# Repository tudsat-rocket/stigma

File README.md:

# Stigma

the core- and mission board for our new flight computer

## Core Board
The core board will be placed on the mission board and will contain all basic and always-needed stuff. Powered by an STM32H7

## Mission Board
The mission board will contain all the other components but may change for future use cases of the core board.

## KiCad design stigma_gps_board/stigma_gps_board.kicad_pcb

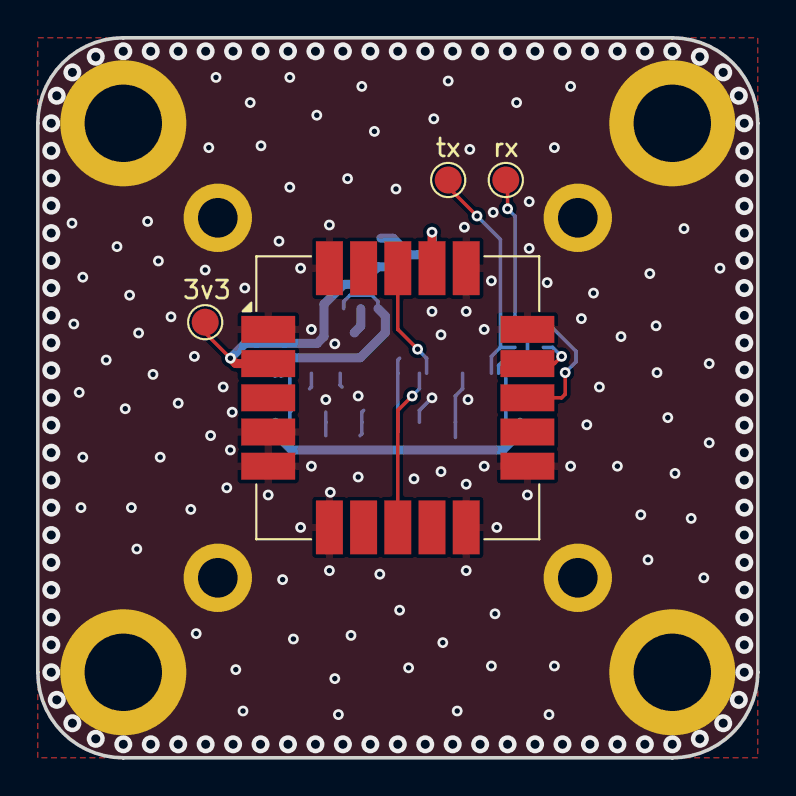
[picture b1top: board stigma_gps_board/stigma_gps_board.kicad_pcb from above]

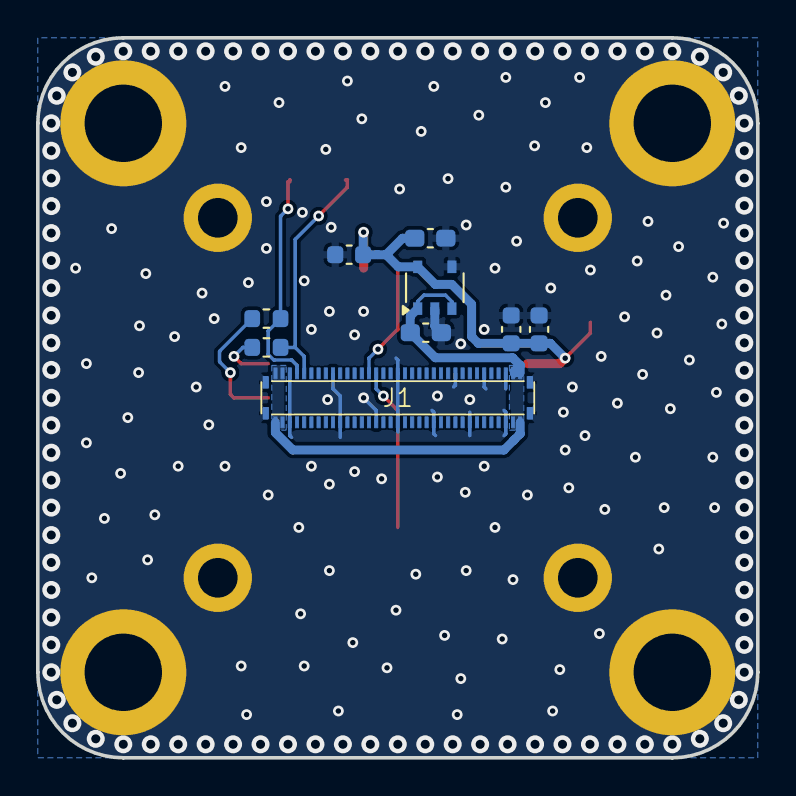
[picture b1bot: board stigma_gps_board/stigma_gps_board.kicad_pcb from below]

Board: 2 copper layers, 40.0 x 40.0 mm, 21 parts (9 on the bottom side), 9 nets.

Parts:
C1, C2: 1uF; C_0603_1608Metric_Pad1.08x0.95mm_HandSolder
C3, C4, C5: 100n; C_0603_1608Metric
H1, H2, H3, H4: MountingHole_Pad; MountingHole_2.2mm_M2_ISO14580_Pad
H5, H6, H7, H8: MountingHole_Pad; MountingHole_4.3mm_M4_ISO14580_Pad
J1: DF40GB-70DP-0.4V; DF40GB-70DP-0.4V-plug
L1, L2: BEAD; L_0603_1608Metric
TP1: tx; TestPoint_Pad_D1.5mm
TP2: rx; TestPoint_Pad_D1.5mm
TP3: 3v3; TestPoint_Pad_D1.5mm
U1: NCP115AMX120TCG; TSOP-5_1.65x3.05mm_P0.95mm
U2: SAM-M10Q; ublox_SAM-M8Q_HandSolder

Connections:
+3.3V: C2.2, C3.2, C4.2, C5.2, TP3.1, U1.5 (OUT), U2.2 (VCC_IO), U2.17 (VCC)
+5V: C1.2, J1.1, J1.2, J1.34, J1.35, J1.36, J1.37, J1.69, J1.70, U1.1 (IN), U1.3 (EN)
GND: C1.1, C2.1, C3.1, C4.1, C5.1, H1.1, H2.1, H3.1, H4.1, H5.1, H6.1, H7.1, H8.1, J1.3, J1.9, J1.18, J1.26, J1.30, J1.33, J1.38, J1.45, J1.50, J1.53, J1.58, J1.63, J1.68, J1.SH (Shield), U1.2 (GND), U1.4 (NC), U2.1 (GND), U2.4 (GND), U2.5 (GND), U2.6 (GND), U2.10 (GND), U2.11 (GND), U2.15 (GND), U2.16 (GND), U2.20 (GND)
GPS_RESET: J1.14, U2.18 (~RESET)
GPS_SAFEBOOT: J1.15, U2.8 (~SAFEBOOT)
unnamed: L1.1, U2.14 (RXD)
unnamed: L2.1, U2.13 (TXD)
UART8_RX_GPS: J1.4, L2.2, TP2.1
UART8_TX_GPS: J1.5, L1.2, TP1.1

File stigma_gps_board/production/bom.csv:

Designator,Footprint,Quantity,Value,LCSC Part #
"C1, C2",0603,2,1uF,C15849
"C3, C4, C5",0603,3,100n,C14663
J1,DF40GB-70DP-0.4V-plug,1,DF40GB-70DP-0.4V,C2692097
L1,0603,1,BEAD,C19330
L2,0603,1,BEAD,
TP1,TestPoint_Pad_D1.5mm,1,tx,
TP2,TestPoint_Pad_D1.5mm,1,rx,
TP3,TestPoint_Pad_D1.5mm,1,3v3,
U1,TSOP-5_1.65x3.05mm_P0.95mm,1,NCP115AMX120TCG,C603505

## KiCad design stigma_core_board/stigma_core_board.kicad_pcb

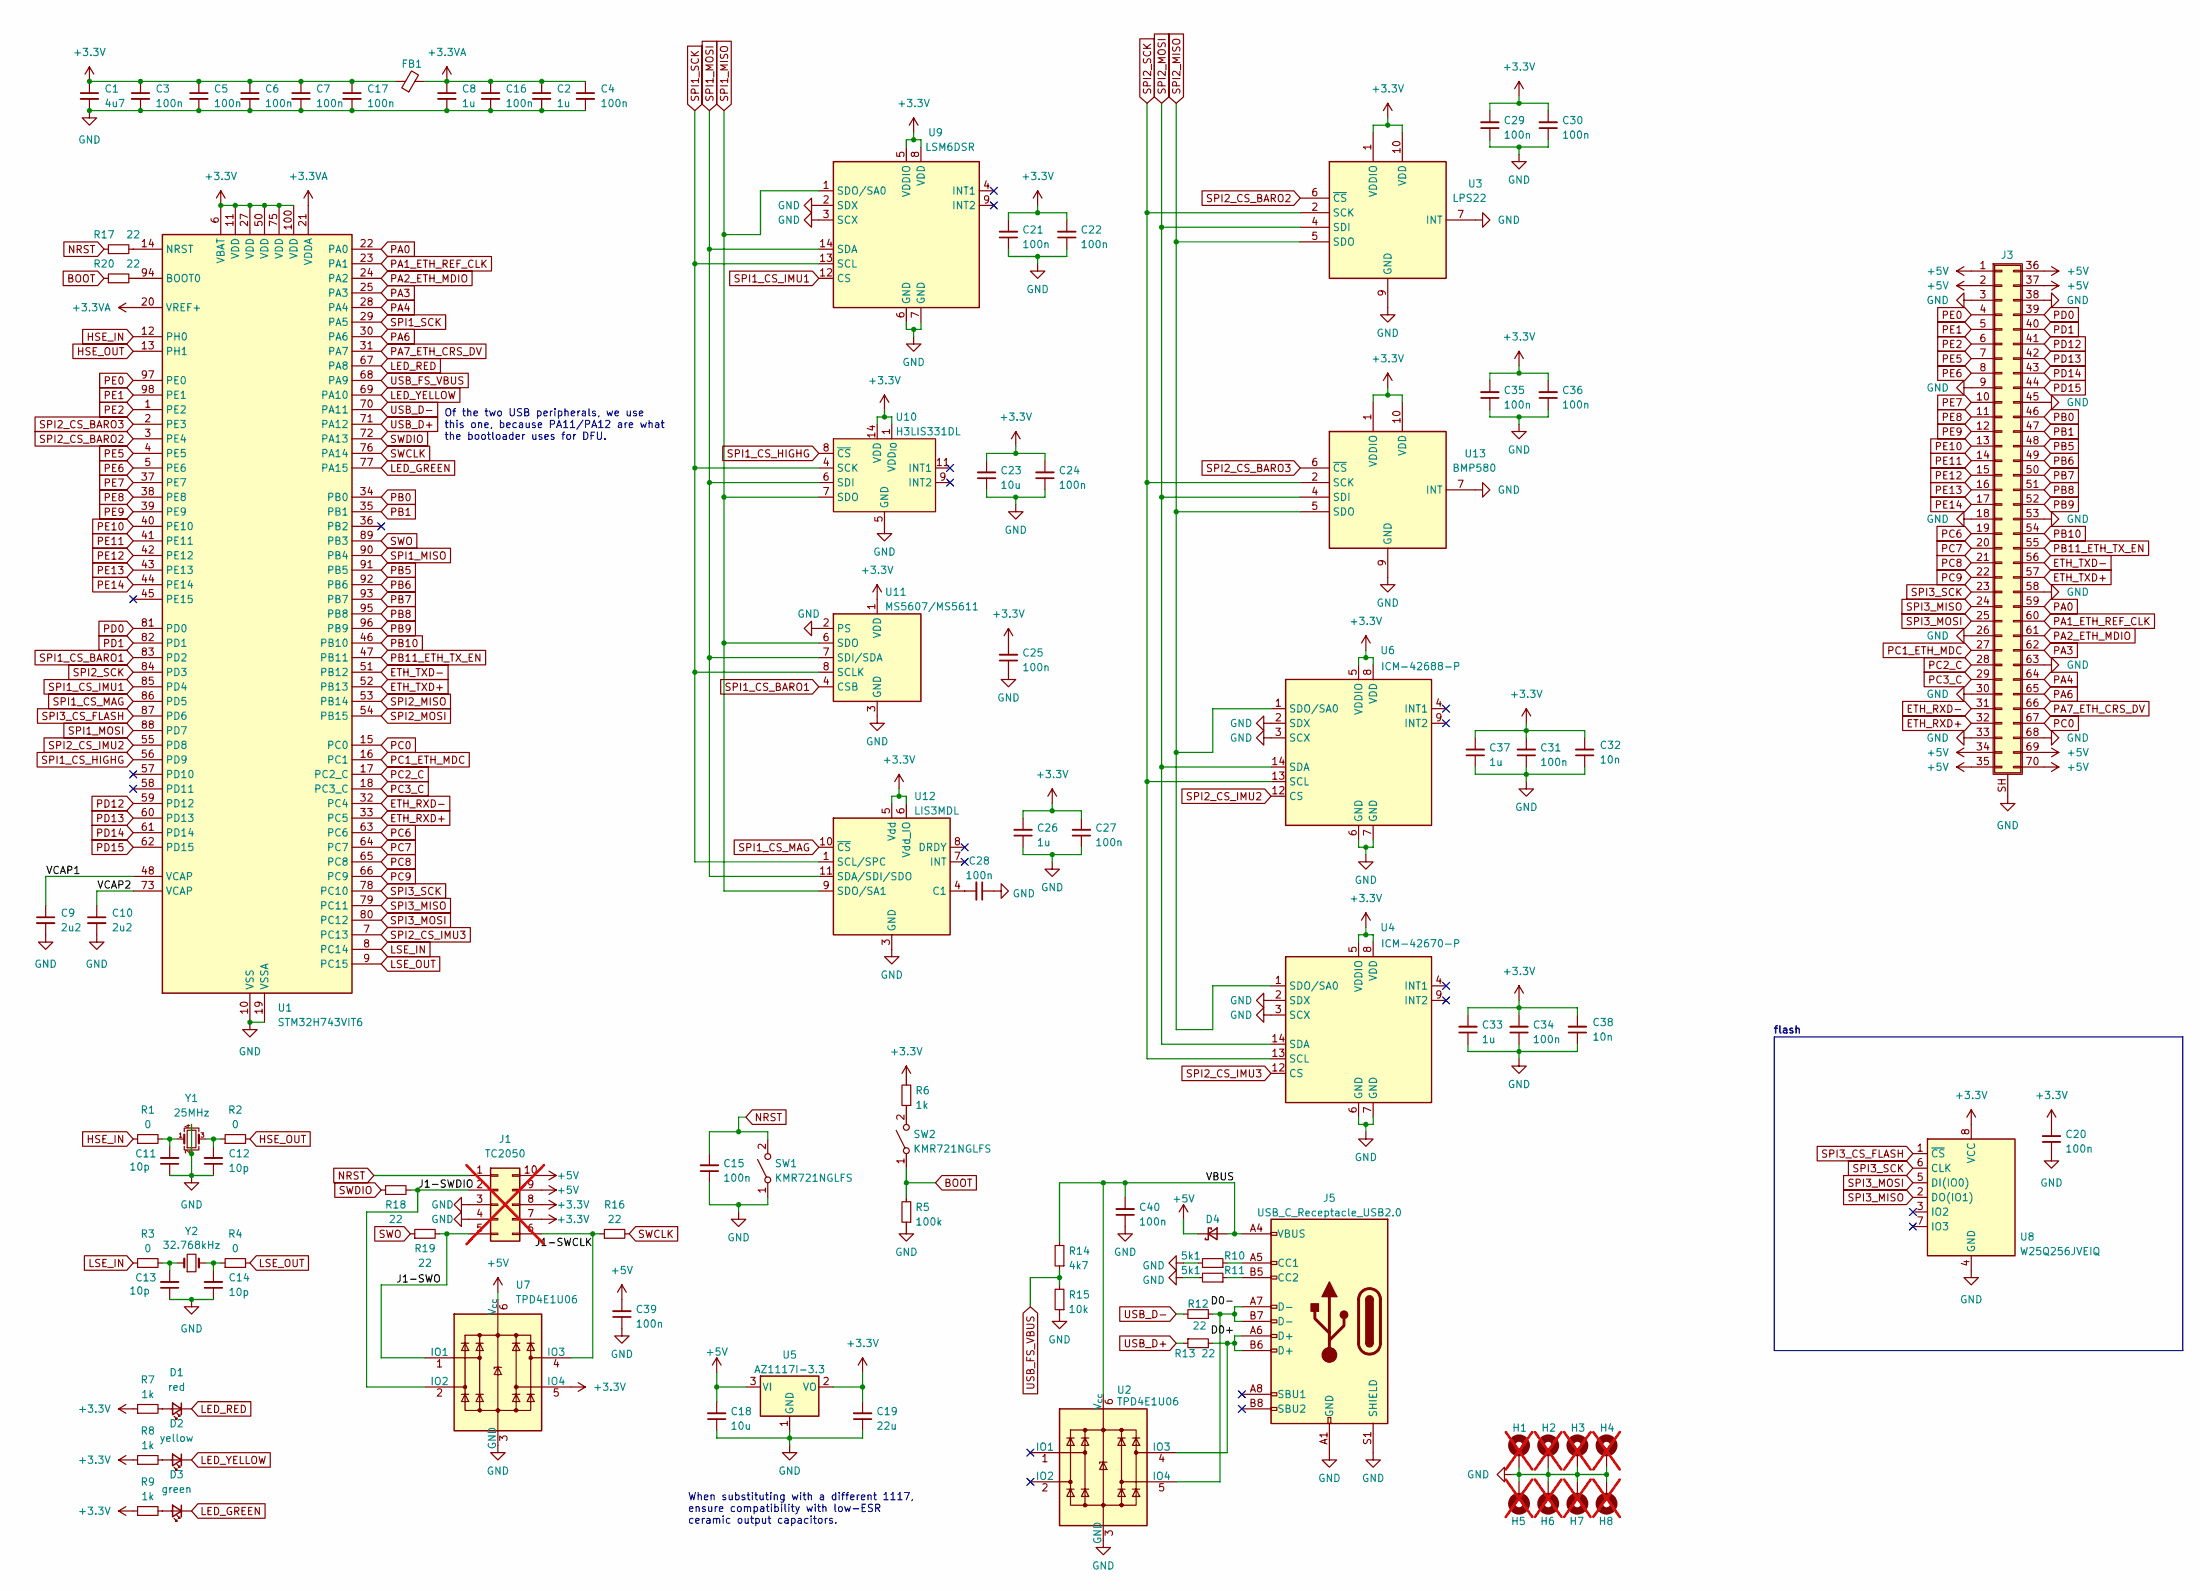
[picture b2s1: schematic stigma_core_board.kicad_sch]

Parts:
C1: 4u7; C_0603_1608Metric; LCSC C19666
C2, C8: 1u; C_0402_1005Metric; LCSC C52923
C3, C4, C5, C6, C7, C16, C17: 100n; C_0402_1005Metric; LCSC C1525
C9, C10: 2u2; C_0402_1005Metric; LCSC C12530
C11, C12, C13, C14: 10p; C_0402_1005Metric; LCSC C32949
C15, C20, C21, C22, C24, C25, C27, C28, C29, C30, C31, C34, C35, C36, C39, C40: 100n; C_0402_1005Metric; Part# CL10B104KB8NNNC; LCSC C1525
C18, C23: 10u; C_0603_1608Metric; Part# CL31B106KAHNNNE; LCSC C19702
C19: 22u; C_0603_1608Metric; Part# CL31A226KAHNNNE; LCSC C86295
C26, C33, C37: 1u; C_0402_1005Metric; Part# CL21A105KBCLNNC; LCSC C52923
C32, C38: 10n; C_0402_1005Metric; Part# CL10B104KB8NNNC; LCSC C15195
D1: red; LED_0603_1608Metric; LCSC C2286
D2: yellow; LED_0603_1608Metric; LCSC C72038
D3: green; LED_0603_1608Metric; LCSC C965804
D4: D_SOD-123; Part# PMEG3020EH,115; LCSC C8598
FB1: FerriteBead_Small; R_0603_1608Metric; LCSC C1002
H1, H2, H3, H4: MountingHole_Pad; MountingHole_4.3mm_M4_ISO14580_Pad; not fitted
H5, H6, H7, H8: MountingHole_Pad; MountingHole_2.2mm_M2_ISO14580_Pad; not fitted
J1: TC2050; Tag-Connect_TC2050-IDC-FP_2x05_P1.27mm_Vertical; not fitted
J3: CONN PLUG 70POS SMD GOLD; DF40GB-70DP-0.4V-plug; LCSC# C2692097
J5: USB_C_Receptacle_USB2.0; USB_C_Receptacle_Palconn_UTC16-G; Part# KH-TYPE-C-16P; LCSC C709357
R1, R2, R3, R4: 0; R_0402_1005Metric; LCSC C17168
R5: 100k; R_0402_1005Metric; Part# RC0603FR-0710KL; LCSC C25741
R6: 1k; R_0402_1005Metric; Part# RC0603FR-0710KL; LCSC C11702
R7, R8, R9: 1k; R_0402_1005Metric; LCSC C11702
R10, R11: 5k1; R_0402_1005Metric; Part# RC0603FR-075K1L; LCSC C25905
R12, R13: 22; R_0402_1005Metric; Part# RC0603FR-0722RL; LCSC C25092
R14: 4k7; R_0402_1005Metric; Part# RC0603FR-0710KL; LCSC C25900
R15: 10k; R_0402_1005Metric; Part# RC0603FR-0710KL; LCSC C25744
R16, R17, R18, R19, R20: 22; R_0402_1005Metric; Part# RC0603FR-0710KL; LCSC C25092
SW1, SW2: KMR721NGLFS; SW_Push_1P1T_NO_CK_KMR2; Part# KMR721NGLFS; LCSC C2911418
U1: STM32H743VIT6; LQFP-100_14x14mm_P0.5mm; LCSC C114409
U2, U7: TPD4E1U06; SOT-563; LCSC C527516
U3: LPS22; ST_HLGA-10_2x2mm_P0.5mm_LayoutBorder3x2y; LCSC C2827824
U4: ICM-42670-P; LGA-14_3x2.5mm_P0.5mm_LayoutBorder3x4y; LCSC C3288646
U5: AZ1117I-3.3; SOT-223-3_TabPin2; Part# AZ1117CH-3.3TRG1; LCSC C92102
U6: ICM-42688-P; LGA-14_3x2.5mm_P0.5mm_LayoutBorder3x4y; Part# LSM6DSRTR; LCSC C1850418
U8: W25Q256JVEIQ; WSON-8-1EP_8x6mm_P1.27mm_EP3.4x4.3mm; LCSC C97522
U9: LSM6DSR; LGA-14_3x2.5mm_P0.5mm_LayoutBorder3x4y; Part# LSM6DSRTR; LCSC C784817
U10: H3LIS331DL; LGA-16_3x3mm_P0.5mm_LayoutBorder3x5y; Part# H3LIS331DLTR; DigiKey# 497-13903-1-ND
U11: MS5607/MS5611; LGA-8_3x5mm_P1.25mm; Part# MS561101BA03-50; DigiKey# 223-1622-1-ND
U12: LIS3MDL; LGA-12_2x2mm_P0.5mm; Part# LIS3MDLTR; DigiKey# 497-13892-1-ND
U13: BMP580; ST_HLGA-10_2x2mm_P0.5mm_LayoutBorder3x2y; LCSC C22391138
Y1: 25MHz; Crystal_SMD_3225-4Pin_3.2x2.5mm; LCSC C9006
Y2: 32.768kHz; Crystal_SMD_3215-2Pin_3.2x1.5mm; LCSC C70509

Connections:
+3.3V: C1.1, C3.1, C5.1, C6.1, C7.1, C17.1, C19.2, C20.2, C21.2, C22.2, C23.2, C24.2, C25.2, C26.2, C27.2, C29.2, C30.2, C31.2, C32.2, C33.2, C34.2, C35.2, C36.2, C37.2, C38.2, FB1.1, J1.7, J1.8, R6.2, R7.1, R8.1, R9.1, U1.6 (VBAT), U1.11 (VDD), U1.27 (VDD), U1.50 (VDD), U1.75 (VDD), U1.100 (VDD), U3.1 (VDDIO), U3.10 (VDD), U4.5 (VDDIO), U4.8 (VDD), U5.2 (VO), U6.5 (VDDIO), U6.8 (VDD), U7.5 (IO4), U8.8 (VCC), U9.5 (VDDIO), U9.8 (VDD), U10.1 (VDD_{IO}), U10.14 (VDD), U10.15 (reserved), U11.1 (VDD), U12.5 (Vdd), U12.6 (Vdd_IO), U13.1 (VDDIO), U13.10 (VDD)
+3.3VA: C2.1, C4.1, C8.1, C16.1, FB1.2, U1.20 (VREF+), U1.21 (VDDA)
+5V: C18.2, C39.2, D4.1 (K), J1.9, J1.10, J3.1, J3.2, J3.34, J3.35, J3.36, J3.37, J3.69, J3.70, U5.3 (VI), U7.6 (V_{cc})
/D0+: J5.A6 (D+), J5.B6 (D+), R13.2, U2.4 (IO3)
/D0-: J5.A7 (D-), J5.B7 (D-), R12.1, U2.5 (IO4)
/J1-SWDIO: J1.2, R18.2, U7.2 (IO2)
/J1-SWO: J1.5, R19.2, U7.1 (IO1)
/VBUS: C40.2, D4.2 (A), J5.A4 (VBUS), J5.A9 (VBUS), J5.B4 (VBUS), J5.B9 (VBUS), R14.2, U2.6 (V_{cc})
/VCAP1: C9.1, U1.48 (VCAP)
/VCAP2: C10.1, U1.73 (VCAP)
BOOT: R5.2, R20.1, SW2.1 (A)
ETH_RXD+: J3.32, U1.33 (PC5)
ETH_RXD-: J3.31, U1.32 (PC4)
ETH_TXD+: J3.57, U1.52 (PB13)
ETH_TXD-: J3.56, U1.51 (PB12)
GND: C1.2, C2.2, C3.2, C4.2, C5.2, C6.2, C7.2, C8.2, C9.2, C10.2, C11.1, C12.1, C13.1, C14.1, C15.1, C16.2, C17.2, C18.1, C19.1, C20.1, C21.1, C22.1, C23.1, C24.1, C25.1, C26.1, C27.1, C28.1, C29.1, C30.1, C31.1, C32.1, C33.1, C34.1, C35.1, C36.1, C37.1, C38.1, C39.1, C40.1, H1.1, H2.1, H3.1, H4.1, H5.1, H6.1, H7.1, H8.1, J1.3, J1.4, J3.3, J3.9, J3.18, J3.26, J3.30, J3.33, J3.38, J3.45, J3.53, J3.58, J3.63, J3.68, J3.SH (Shield), J5.A1 (GND), J5.A12 (GND), J5.B1 (GND), J5.B12 (GND), J5.S1 (SHIELD), R5.1, R10.2, R11.2, R15.1, SW1.1 (A), U1.10 (VSS), U1.19 (VSSA), U1.26 (VSS), U1.49 (VSS), U1.74 (VSS), U1.99 (VSS), U2.3 (GND), U3.3 (GND), U3.7 (INT), U3.8 (GND), U3.9 (GND), U4.2 (SDX), U4.3 (SCX), U4.6 (GND), U4.7 (GND), U5.1 (GND), U6.2 (SDX), U6.3 (SCX), U6.6 (GND), U6.7 (GND), U7.3 (GND), U8.4 (GND), U9.2 (SDX), U9.3 (SCX), U9.6 (GND), U9.7 (GND), U10.5 (GND), U10.10 (reserved), U10.12 (GND), U10.13 (GND), U10.16 (GND), U11.2 (PS), U11.3 (GND), U12.2 (GND), U12.3 (GND), U12.12 (GND), U13.3 (GND), U13.7 (INT), U13.8 (GND), U13.9 (GND), Y1.2, Y1.4
HSE_IN: R1.1, U1.12 (PH0)
HSE_OUT: R2.2, U1.13 (PH1)
LED_GREEN: D3.1 (K), U1.77 (PA15)
LED_RED: D1.1 (K), U1.67 (PA8)
LED_YELLOW: D2.1 (K), U1.69 (PA10)
LSE_IN: R3.1, U1.8 (PC14)
LSE_OUT: R4.2, U1.9 (PC15)
NRST: C15.2, J1.1, R17.1, SW1.2 (B)
unnamed: C11.2, R1.2, Y1.1
unnamed: C12.2, R2.1, Y1.3
unnamed: C13.2, R3.2, Y2.1
unnamed: C14.2, R4.1, Y2.2
unnamed: D1.2 (A), R7.2
unnamed: D2.2 (A), R8.2
unnamed: D3.2 (A), R9.2
unnamed: J1.6, R16.1, U7.4 (IO3)
unnamed: J5.A5 (CC1), R10.1
unnamed: J5.B5 (CC2), R11.1
unnamed: R6.1, SW2.2 (B)
unnamed: R20.2, U1.94 (BOOT0)
unnamed: R17.2, U1.14 (NRST)
unnamed: C28.2, U12.4 (C1)
PA0: J3.59, U1.22 (PA0)
PA1_ETH_REF_CLK: J3.60, U1.23 (PA1)
PA2_ETH_MDIO: J3.61, U1.24 (PA2)
PA3: J3.62, U1.25 (PA3)
PA4: J3.64, U1.28 (PA4)
PA6: J3.65, U1.30 (PA6)
PA7_ETH_CRS_DV: J3.66, U1.31 (PA7)
PB0: J3.46, U1.34 (PB0)
PB1: J3.47, U1.35 (PB1)
PB5: J3.48, U1.91 (PB5)
PB6: J3.49, U1.92 (PB6)
PB7: J3.50, U1.93 (PB7)
PB8: J3.51, U1.95 (PB8)
PB9: J3.52, U1.96 (PB9)
PB10: J3.54, U1.46 (PB10)
PB11_ETH_TX_EN: J3.55, U1.47 (PB11)
PC0: J3.67, U1.15 (PC0)
PC1_ETH_MDC: J3.27, U1.16 (PC1)
PC2_C: J3.28, U1.17 (PC2_C)
PC3_C: J3.29, U1.18 (PC3_C)
PC6: J3.19, U1.63 (PC6)
PC7: J3.20, U1.64 (PC7)
PC8: J3.21, U1.65 (PC8)
PC9: J3.22, U1.66 (PC9)
PD0: J3.39, U1.81 (PD0)
PD1: J3.40, U1.82 (PD1)
PD12: J3.41, U1.59 (PD12)
PD13: J3.42, U1.60 (PD13)
PD14: J3.43, U1.61 (PD14)
PD15: J3.44, U1.62 (PD15)
PE0: J3.4, U1.97 (PE0)
PE1: J3.5, U1.98 (PE1)
PE2: J3.6, U1.1 (PE2)
PE5: J3.7, U1.4 (PE5)
PE6: J3.8, U1.5 (PE6)
PE7: J3.10, U1.37 (PE7)
PE8: J3.11, U1.38 (PE8)
PE9: J3.12, U1.39 (PE9)
PE10: J3.13, U1.40 (PE10)
PE11: J3.14, U1.41 (PE11)
PE12: J3.15, U1.42 (PE12)
PE13: J3.16, U1.43 (PE13)
PE14: J3.17, U1.44 (PE14)
SPI1_CS_BARO1: U1.83 (PD2), U11.4 (CSB), U11.5 (CSB)
SPI1_CS_HIGHG: U1.56 (PD9), U10.8 (~CS)
SPI1_CS_IMU1: U1.85 (PD4), U9.12 (CS)
SPI1_CS_MAG: U1.86 (PD5), U12.10 (~CS)
SPI1_MISO: U1.90 (PB4), U9.1 (SDO/SA0), U10.7 (SDO), U11.6 (SDO), U12.9 (SDO/SA1)
SPI1_MOSI: U1.88 (PD7), U9.14 (SDA), U10.6 (SDI), U11.7 (SDI/SDA), U12.11 (SDA/SDI/SDO)
SPI1_SCK: U1.29 (PA5), U9.13 (SCL), U10.4 (SCK), U11.8 (SCLK), U12.1 (SCL/SPC)
SPI2_CS_BARO2: U1.3 (PE4), U3.6 (~CS)
SPI2_CS_BARO3: U1.2 (PE3), U13.6 (~CS)
SPI2_CS_IMU2: U1.55 (PD8), U6.12 (CS)
SPI2_CS_IMU3: U1.7 (PC13), U4.12 (CS)
SPI2_MISO: U1.53 (PB14), U3.5 (SDO), U4.1 (SDO/SA0), U6.1 (SDO/SA0), U13.5 (SDO)
SPI2_MOSI: U1.54 (PB15), U3.4 (SDI), U4.14 (SDA), U6.14 (SDA), U13.4 (SDI)
SPI2_SCK: U1.84 (PD3), U3.2 (SCK), U4.13 (SCL), U6.13 (SCL), U13.2 (SCK)
SPI3_CS_FLASH: U1.87 (PD6), U8.1 (~CS)
SPI3_MISO: J3.24, U1.79 (PC11), U8.2 (DO(IO1))
SPI3_MOSI: J3.25, U1.80 (PC12), U8.5 (DI(IO0))
SPI3_SCK: J3.23, U1.78 (PC10), U8.6 (CLK)
SWCLK: R16.2, U1.76 (PA14)
SWDIO: R18.1, U1.72 (PA13)
SWO: R19.1, U1.89 (PB3)
USB_D+: R13.1, U1.71 (PA12)
USB_D-: R12.2, U1.70 (PA11)
USB_FS_VBUS: R14.1, R15.2, U1.68 (PA9)

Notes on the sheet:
Of the two USB peripherals, we use this one, because PA11/PA12 are what the bootloader uses for DFU.
flash
When substituting with a different 1117, ensure compatibility with low-ESR ceramic output capacitors.

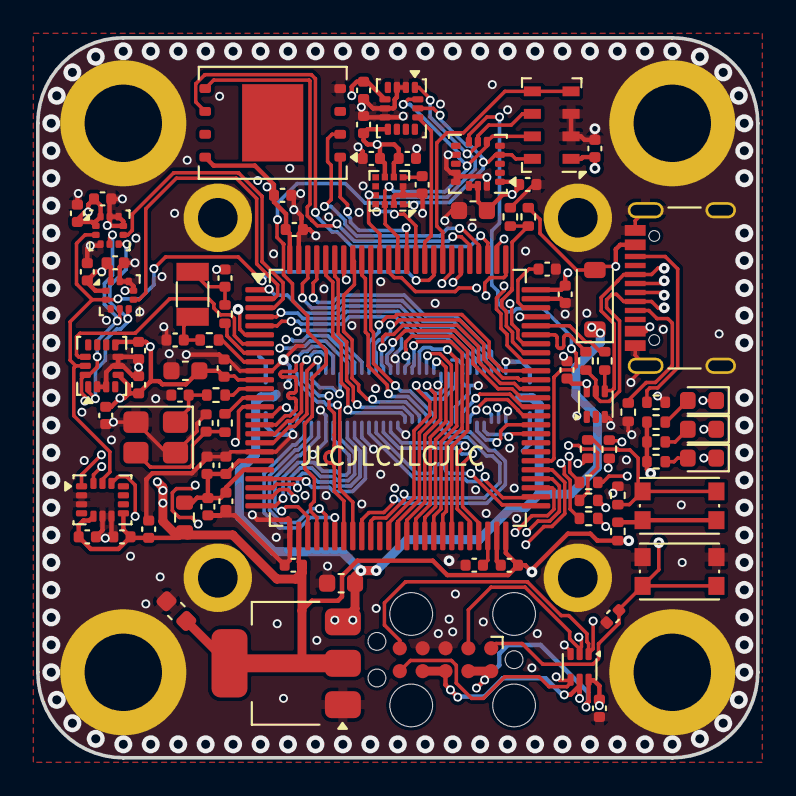
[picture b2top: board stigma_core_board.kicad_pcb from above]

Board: 4 copper layers, 40.0 x 40.0 mm, 93 parts (1 on the bottom side), 105 nets.

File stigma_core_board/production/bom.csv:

Designator,Footprint,Quantity,Value,LCSC Part #
C1,0603,1,4u7,C19666
"C10, C9",0402,2,2u2,C12530
"C11, C12, C13, C14",0402,4,10p,C32949
"C15, C16, C17, C20, C21, C22, C24, C25, C27, C28, C29, C3, C30, C31, C34, C35, C36, C39, C4, C40, C5, C6, C7",0402,23,100n,C1525
"C18, C23",0603,2,10u,C19702
C19,0603,1,22u,C86295
"C2, C26, C33, C37, C8",0402,5,1u,C52923
"C32, C38",0402,2,10n,C15195
D1,0603,1,red,C2286
D2,0603,1,yellow,C72038
D3,0603,1,green,C965804
D4,D_SOD-123,1,~,C8598
FB1,0603,1,FerriteBead_Small,C1002
J1,Tag-Connect_TC2050-IDC-FP_2x05_P1.27mm_Vertical,1,TC2050,
J3,DF40GB-70DP-0.4V-plug,1,CONN PLUG 70POS SMD GOLD,
J5,USB_C_Receptacle_Palconn_UTC16-G,1,USB_C_Receptacle_USB2.0,C709357
"R1, R2, R3, R4",0402,4,0,C17168
"R10, R11",0402,2,5k1,C25905
"R12, R13, R16, R17, R18, R19, R20",0402,7,22,C25092
R14,0402,1,4k7,C25900
R15,0402,1,10k,C25744
R5,0402,1,100k,C25741
"R6, R7, R8, R9",0402,4,1k,C11702
"SW1, SW2",SW_Push_1P1T_NO_CK_KMR2,2,KMR721NGLFS,C2911418
U1,LQFP-100_14x14mm_P0.5mm,1,STM32H743VIT6,C114409
U10,LGA-16_3x3mm_P0.5mm_LayoutBorder3x5y,1,H3LIS331DL,C2655074
U11,LGA-8_3x5mm_P1.25mm,1,MS5607/MS5611,C97627
U12,LGA-12_2x2mm_P0.5mm,1,LIS3MDL,C478483
U13,ST_HLGA-10_2x2mm_P0.5mm_LayoutBorder3x2y,1,BMP580,C22391138
"U2, U7",SOT-563,2,TPD4E1U06,C527516
U3,ST_HLGA-10_2x2mm_P0.5mm_LayoutBorder3x2y,1,LPS22,C2827824
U4,LGA-14_3x2.5mm_P0.5mm_LayoutBorder3x4y,1,ICM-42670-P,C3288646
U5,SOT-223-3_TabPin2,1,AZ1117I-3.3,C92102
U6,LGA-14_3x2.5mm_P0.5mm_LayoutBorder3x4y,1,ICM-42688-P,C1850418
U8,WSON-8-1EP_8x6mm_P1.27mm_EP3.4x4.3mm,1,W25Q256JVEIQ,C97522
U9,LGA-14_3x2.5mm_P0.5mm_LayoutBorder3x4y,1,LSM6DSR,C784817
Y1,Crystal_SMD_3225-4Pin_3.2x2.5mm,1,25MHz,C9006
Y2,Crystal_SMD_3215-2Pin_3.2x1.5mm,1,32.768kHz,C70509

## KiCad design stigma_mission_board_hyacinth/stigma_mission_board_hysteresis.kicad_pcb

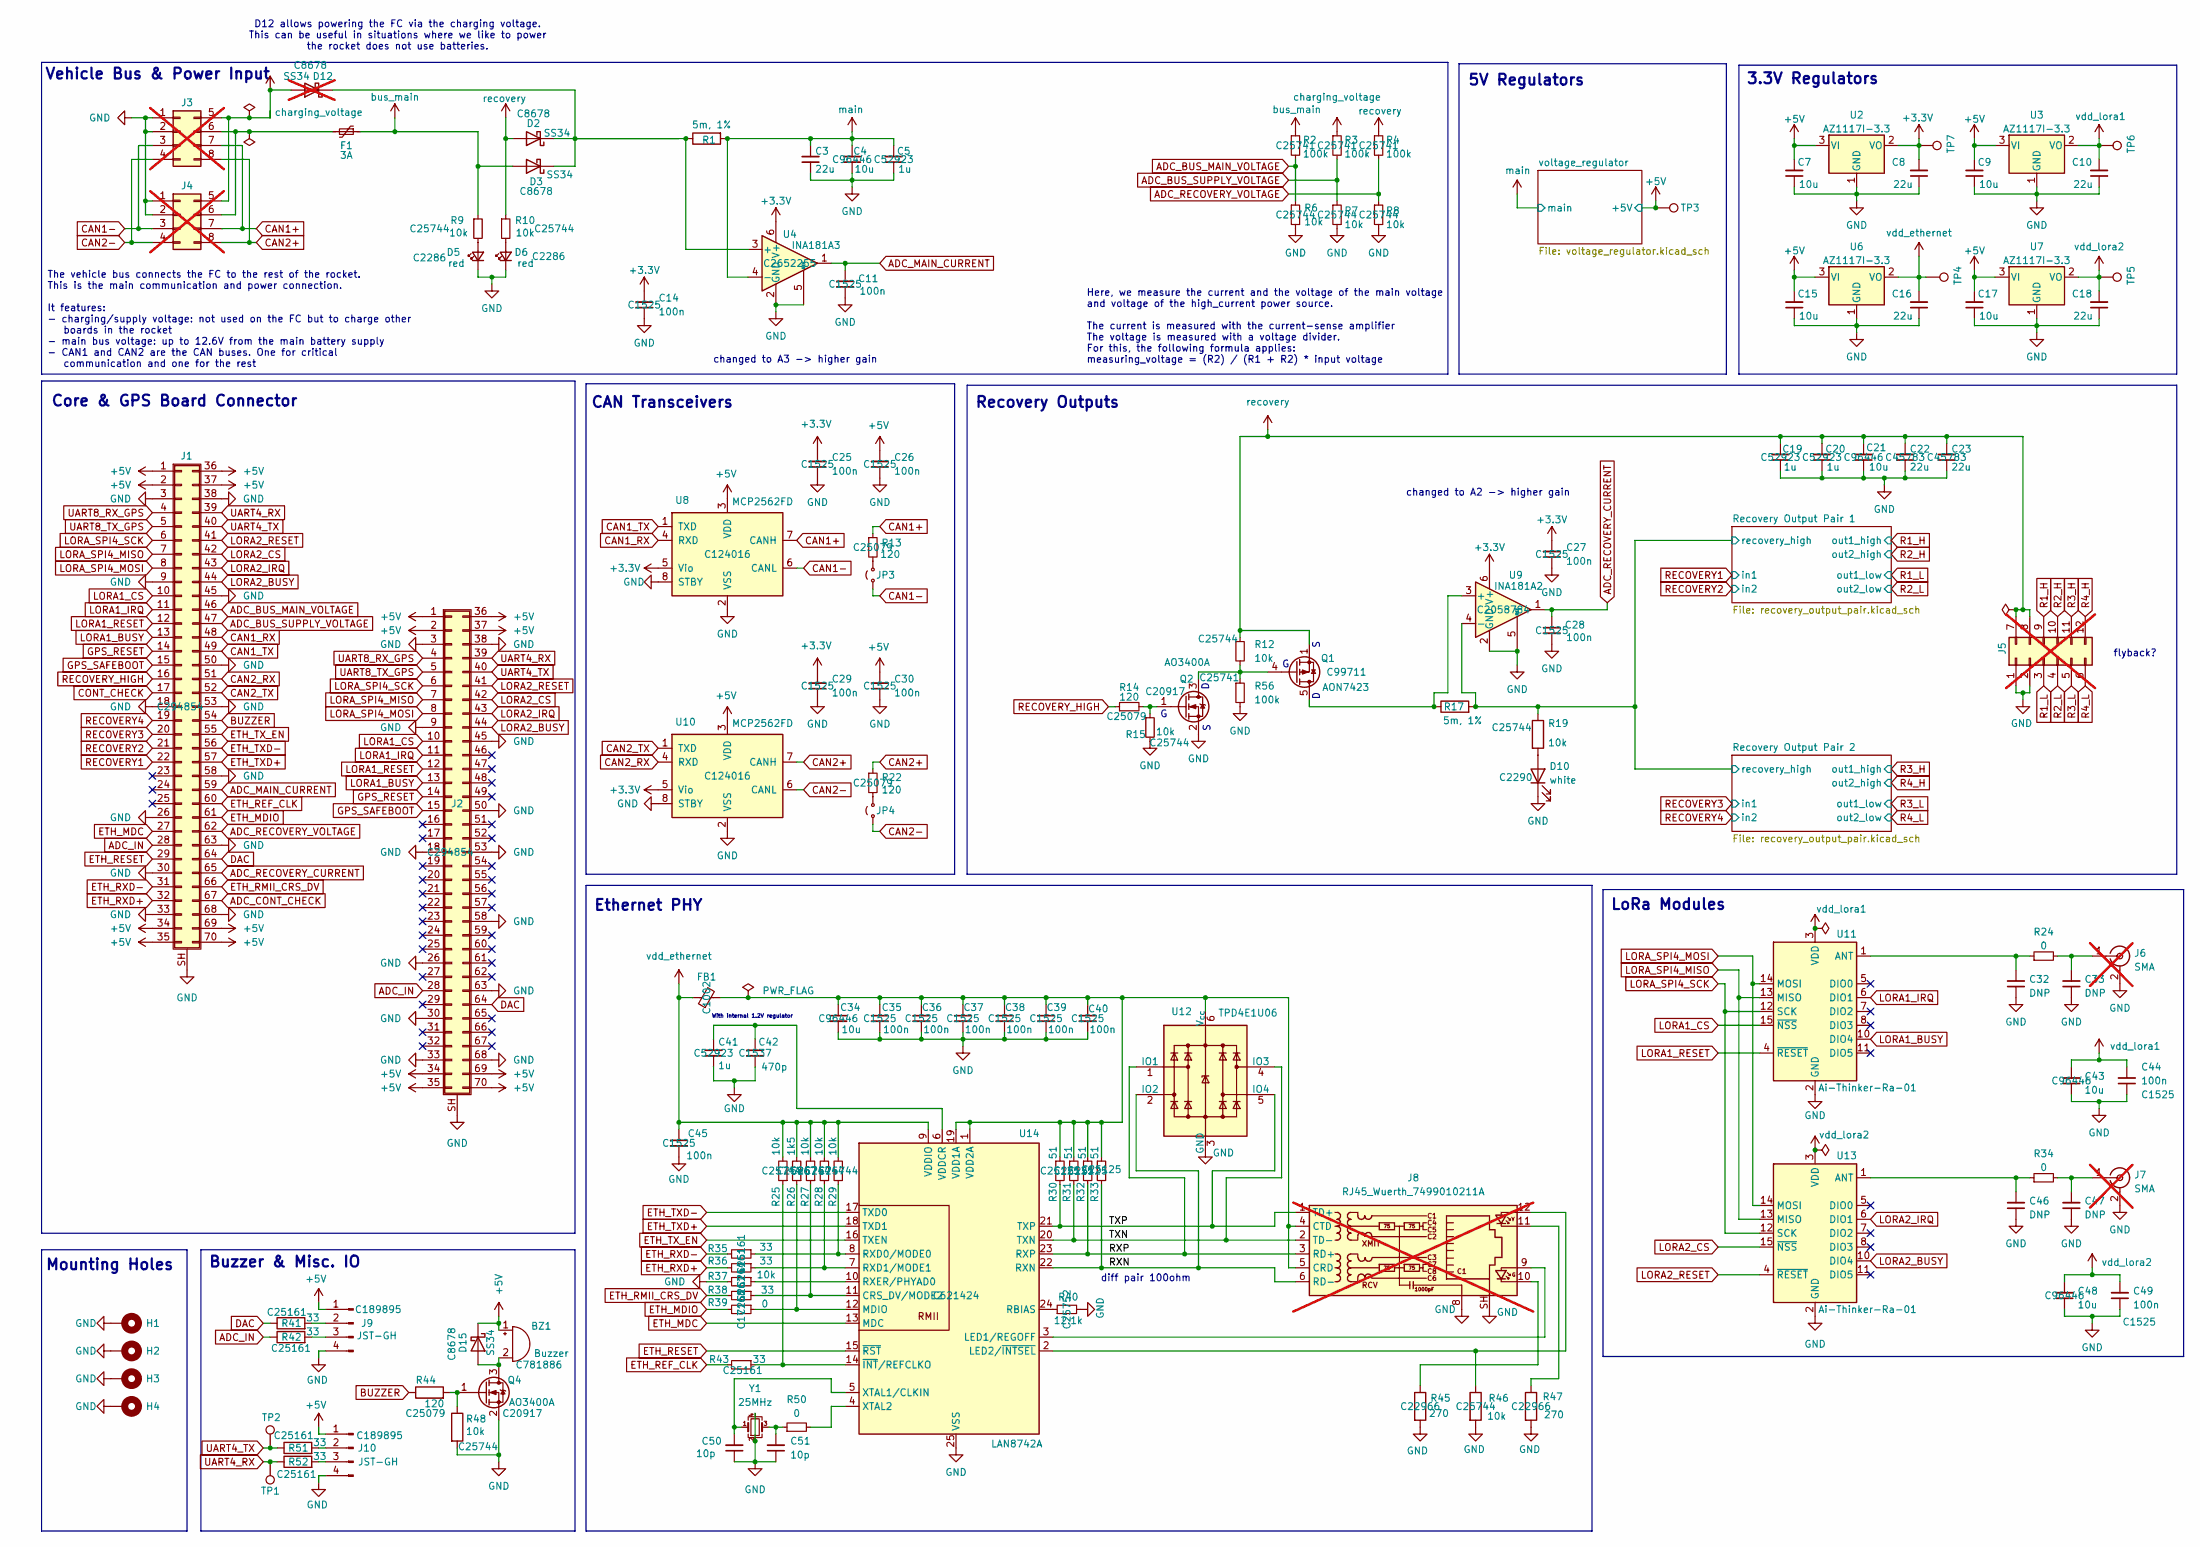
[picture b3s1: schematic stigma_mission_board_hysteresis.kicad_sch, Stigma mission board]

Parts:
BZ1: Buzzer; MagneticBuzzer_CUI_CMT-8504-100-SMT; Part# CMT-8504-100-SMT-TR; DigiKey# 102-CMT-8504-100-SMT-CT-ND
C3: 22u; C_0805_2012Metric; LCSC C45783
C4, C21: 10u; C_0603_1608Metric; Part# CS2012X7R106M100NRE; LCSC C96446
C5, C19, C20: 1u; C_0402_1005Metric; Part# CS1608X5R105K250NRB; LCSC C52923
C7, C9, C15, C17, C43, C48: 10u; C_0603_1608Metric; Part# CL31B106KAHNNNE; LCSC C96446
C8, C10, C16, C18: 22u; C_0805_2012Metric; Part# CL31A226KAHNNNE; LCSC C45783
C11, C14, C25, C26, C27, C28, C29, C30, C35, C36, C37, C38, C39, C40, C45: 100n; C_0402_1005Metric; LCSC C1525
C22, C23: 22u; C_0805_2012Metric; Part# CS2012X5R226M250NRE; LCSC C45783
C32, C33, C46, C47: DNP; C_0603_1608Metric
C34: 10u; C_0603_1608Metric; LCSC C96446
C41: 1u; C_0402_1005Metric; LCSC C52923
C42: 470p; C_0402_1005Metric; LCSC C1537
C44, C49: 100n; C_0402_1005Metric; Part# CL10B104KB8NNNC; LCSC C1525
C50, C51: 10p; C_0402_1005Metric; LCSC C32949
D2, D3, D15: SS34; D_SMA; LCSC C8678
D5, D6: red; LED_0603_1608Metric; LCSC C2286
D10: white; LED_0603_1608Metric; LCSC C2290
D12: SS34; D_SMA; LCSC C8678; not fitted
F1: 3A; Fuse_1206_3216Metric_Pad1.42x1.75mm_HandSolder; Part# 0467003.NRHF; LCSC C99558
FB1: FerriteBead; L_0603_1608Metric; LCSC C1002
H1, H2, H3, H4: MountingHole_Pad; MountingHole_3.2mm_M3_Pad_Via; Part# N/A; DigiKey# N/A
J1, J2: DF40C-70DS-0.4V(51); core-board-inner-mounting-holes; LCSC C294854
J3, J4: Molex_Micro-Fit_3.0_43045-0800_2x04_P3.00mm_Horizontal; not fitted
J5: Molex_Micro-Fit_3.0_43045-1200_2x06_P3.00mm_Horizontal; not fitted
J6, J7: SMA; SMA_Amphenol_132289_EdgeMount; not fitted
J8: RJ45_Wuerth_7499010211A; RJ45_Wuerth_7499010211A_Horizontal; not fitted
J9, J10: JST-GH; JST_GH_SM04B-GHS-TB_1x04-1MP_P1.25mm_Horizontal; LCSC C189895
JP3, JP4: Jumper_2_Small_Open; PinHeader_1x02_P1.27mm_Vertical
Q1: AON7423; DFN-8-1EP_3x3mm_P0.65mm_EP1.55x2.4mm; LCSC C99711
Q2, Q4: AO3400A; SOT-23; LCSC C20917
R1, R17: 5m, 1%; R_2512_6332Metric; LCSC C723630
R2, R3, R4: 100k; R_0402_1005Metric; Part# RC0603FR-071K8L; LCSC C25741
R6, R7, R8, R12: 10k; R_0402_1005Metric; Part# RC0603FR-071KL; LCSC C25744
R9, R10: 10k; R_0402_1005Metric; Part# ESR03EZPJ221; LCSC C25744
R13, R22: 120; R_0402_1005Metric; Part# RC0603FR-07120RL; LCSC C25079
R14: 120; R_0402_1005Metric; Part# RC0603FR-071KL; LCSC C25079
R15, R19, R25, R27, R28, R29, R37, R46, R48: 10k; R_0402_1005Metric; LCSC C25744
R24, R34: 0; R_0603_1608Metric; Part# RC0603FR-070RL
R26: 1k5; R_0402_1005Metric; LCSC C25867
R30, R31, R32, R33: 51; R_0402_1005Metric; LCSC C25125
R35, R36, R38, R41, R42, R43, R51, R52: 33; R_0402_1005Metric; LCSC C25161
R39, R50: 0; R_0402_1005Metric; LCSC C17168
R40: 12.1k; R_0402_1005Metric; LCSC C25752
R44: 120; R_0402_1005Metric; LCSC C25079
R45, R47: 270; R_0603_1608Metric; LCSC C22966
R56: 100k; R_0402_1005Metric; Part# RC0603FR-071KL; LCSC C25741
TP1, TP2, TP3, TP4, TP5, TP6, TP7: TestPoint; TestPoint_Pad_D1.5mm
U2, U3, U6, U7: AZ1117I-3.3; SOT-223-3_TabPin2; Part# AZ1117CH-3.3TRG1; LCSC C92102
U4: INA181A3; SOT-23-6; LCSC C2652255
U8, U10: MCP2562FD; SOIC-8_3.9x4.9mm_P1.27mm; LCSC C124016
U9: INA181A2; SOT-23-6; LCSC C2058784
U11, U13: Ai-Thinker-Ra-01; Ai-Thinker-Ra-01-LoRa
U12: TPD4E1U06; SOT-563; LCSC C527516
U14: LAN8742A; VQFN-24-1EP_4x4mm_P0.5mm_EP2.5x2.5mm_ThermalVias; LCSC C621424
Y1: 25MHz; Crystal_SMD_3225-4Pin_3.2x2.5mm; LCSC C9006

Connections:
+3.3V: C8.2, C14.2, C25.2, C27.2, C29.2, TP7.1, U2.2 (VO), U4.6 (V+), U8.5 (Vio), U9.6 (V+), U10.5 (Vio)
+5V: BZ1.1 (-), C7.2, C9.2, C15.2, C17.2, C26.2, C30.2, D15.1 (K), J1.1, J1.2, J1.34, J1.35, J1.36, J1.37, J1.69, J1.70, J2.1, J2.2, J2.34, J2.35, J2.36, J2.37, J2.69, J2.70, J9.1, J10.1, TP3.1, U2.3 (VI), U3.3 (VI), U6.3 (VI), U7.3 (VI), U8.3 (VDD), U10.3 (VDD); also elsewhere on the board
/RXN: J8.6 (RD-), R33.2, U12.2 (IO2), U14.22 (RXN)
/RXP: J8.3 (RD+), R32.2, U12.1 (IO1), U14.23 (RXP)
/Recovery Output Pair 1/recovery_high: R17.2, R19.1, U9.4 (-); also elsewhere on the board
/TXN: J8.2 (TD-), R31.2, U12.4 (IO3), U14.20 (TXN)
/TXP: J8.1 (TD+), R30.2, U12.5 (IO4), U14.21 (TXP)
ADC_BUS_MAIN_VOLTAGE: J1.46, R2.2, R6.1
ADC_BUS_SUPPLY_VOLTAGE: J1.47, R3.2, R7.1
ADC_CONT_CHECK: J1.67
ADC_IN: J1.28, J2.28, R42.1
ADC_MAIN_CURRENT: C11.1, J1.59, U4.1
ADC_RECOVERY_CURRENT: C28.1, J1.65, U9.1
ADC_RECOVERY_VOLTAGE: J1.62, R4.2, R8.1
BUZZER: J1.54, R44.1
CAN1+: J3.7, J4.7, R13.1, U8.7 (CANH)
CAN1-: J3.3, J4.3, JP3.1 (A), U8.6 (CANL)
CAN1_RX: J1.48, U8.4 (RXD)
CAN1_TX: J1.49, U8.1 (TXD)
CAN2+: J3.8, J4.8, R22.1, U10.7 (CANH)
CAN2-: J3.4, J4.4, JP4.1 (A), U10.6 (CANL)
CAN2_RX: J1.51, U10.4 (RXD)
CAN2_TX: J1.52, U10.1 (TXD)
CONT_CHECK: J1.17
DAC: J1.64, J2.64, R41.1
ETH_MDC: J1.27, U14.13 (MDC)
ETH_MDIO: J1.61, R39.2
ETH_REF_CLK: J1.60, R43.2
ETH_RESET: J1.29, U14.15 (~RST)
ETH_RMII_CRS_DV: J1.66, R38.2
ETH_RXD+: J1.32, R36.2
ETH_RXD-: J1.31, R35.2
ETH_TXD+: J1.57, U14.18 (TXD1)
ETH_TXD-: J1.56, U14.17 (TXD0)
ETH_TX_EN: J1.55, U14.16 (TXEN)
GND: C3.1, C4.1, C5.1, C7.1, C8.1, C9.1, C10.1, C11.2, C14.1, C15.1, C16.1, C17.1, C18.1, C19.1, C20.1, C21.1, C22.1, C23.1, C25.1, C26.1, C27.1, C28.2, C29.1, C30.1, C32.1, C33.1, C34.2, C35.2, C36.2, C37.2, C38.2, C39.2, C40.2, C41.2, C42.2, C43.1, C44.1, C45.2, C46.1, C47.1, C48.1, C49.1, C50.1, C51.1, D5.1 (K), D6.1 (K), D10.1 (K), H1.1, H2.1, H3.1, H4.1, J1.3, J1.9, J1.18, J1.26, J1.30, J1.33, J1.38, J1.45, J1.50, J1.53, J1.58, J1.63, J1.68, J1.SH (Shield), J2.3, J2.9, J2.18, J2.26, J2.30, J2.33, J2.38, J2.45, J2.50, J2.53, J2.58, J2.63, J2.68, J2.SH (Shield), J3.1, J3.2, J4.1, J4.2, J5.1, J5.2, J6.2 (Ext), J7.2 (Ext), J8.8, J8.SH, J9.4, J10.4, Q2.2 (S), Q4.2 (S), R6.2, R7.2, R8.2, R15.2, R37.2, R40.2, R45.2, R46.2, R47.2, R48.2, R56.2, U2.1 (GND), U3.1 (GND), U4.2 (GND), U4.5 (REF), U6.1 (GND), U7.1 (GND), U8.2 (VSS), U8.8 (STBY), U9.2 (GND), U9.5 (REF), U10.2 (VSS), U10.8 (STBY), U11.2 (GND), U11.9 (GND), U11.16 (GND), U12.3 (GND), U13.2 (GND), U13.9 (GND), U13.16 (GND), U14.25 (VSS), Y1.2, Y1.4; also elsewhere on the board
GPS_RESET: J1.14, J2.14
GPS_SAFEBOOT: J1.15, J2.15
LORA1_BUSY: J1.13, J2.13, U11.10 (DIO4)
LORA1_CS: J1.10, J2.10, U11.15 (~NSS)
LORA1_IRQ: J1.11, J2.11, U11.6 (DIO1)
LORA1_RESET: J1.12, J2.12, U11.4 (~RESET)
LORA2_BUSY: J1.44, J2.44, U13.10 (DIO4)
LORA2_CS: J1.42, J2.42, U13.15 (~NSS)
LORA2_IRQ: J1.43, J2.43, U13.6 (DIO1)
LORA2_RESET: J1.41, J2.41, U13.4 (~RESET)
LORA_SPI4_MISO: J1.7, J2.7, U11.13 (MISO), U13.13 (MISO)
LORA_SPI4_MOSI: J1.8, J2.8, U11.14 (MOSI), U13.14 (MOSI)
LORA_SPI4_SCK: J1.6, J2.6, U11.12 (SCK), U13.12 (SCK)
unnamed: BZ1.2 (+), D15.2 (A), Q4.3 (D)
unnamed: C51.2, R50.1, Y1.3
unnamed: D5.2 (A), R9.2
unnamed: D6.2 (A), R10.2
unnamed: D10.2 (A), R19.2
unnamed: D2.1 (K), D3.1 (K), D12.1 (K), R1.1, U4.3 (+)
unnamed: F1.2, J3.6, J4.6
unnamed: C33.2, J6.1 (In), R24.2
unnamed: C47.2, J7.1 (In), R34.2
unnamed: C34.1, C35.1, C36.1, C37.1, C38.1, C39.1, C40.1, FB1.2, J8.4 (CTD), J8.5 (CRD), R30.1, R31.1, R32.1, R33.1, U12.6 (V_{cc}), U14.1 (VDD2A), U14.19 (VDD1A)
unnamed: J8.10, R45.1
unnamed: J8.11, R47.1
unnamed: J9.2, R41.2
unnamed: J9.3, R42.2
unnamed: J10.2, R51.2
unnamed: J10.3, R52.2
unnamed: JP3.2 (B), R13.2
unnamed: JP4.2 (B), R22.2
unnamed: Q1.4 (G), Q2.3 (D), R12.2, R56.1
unnamed: Q2.1 (G), R14.2, R15.1
unnamed: Q4.1 (G), R44.2, R48.1
unnamed: Q1.5 (D), Q1.6 (D), Q1.7 (D), Q1.8 (D), Q1.9 (D), R17.1, U9.3 (+)
unnamed: C32.2, R24.1, U11.1 (ANT)
unnamed: C46.2, R34.1, U13.1 (ANT)
unnamed: R27.1, R38.1, U14.11 (CRS_DV/MODE2)
unnamed: J8.9, U14.3 (LED1/REGOFF)
unnamed: J8.12, R46.1, U14.2 (LED2/~INTSEL)
unnamed: R26.1, R39.1, U14.12 (MDIO)
unnamed: R40.1, U14.24 (RBIAS)
unnamed: R29.1, R35.1, U14.8 (RXD0/MODE0)
unnamed: R28.1, R36.1, U14.7 (RXD1/MODE1)
unnamed: R37.1, U14.10 (RXER/PHYAD0)
unnamed: C41.1, C42.1, U14.6 (VDDCR)
unnamed: C50.2, U14.5 (XTAL1/CLKIN), Y1.1
unnamed: R50.2, U14.4 (XTAL2)
unnamed: R25.1, R43.1, U14.14 (~INT/REFCLKO)
R1_H: J5.9; also elsewhere on the board
R1_L: J5.3; also elsewhere on the board
R2_H: J5.10; also elsewhere on the board
R2_L: J5.4; also elsewhere on the board
R3_H: J5.11; also elsewhere on the board
R3_L: J5.5; also elsewhere on the board
R4_H: J5.12; also elsewhere on the board
R4_L: J5.6; also elsewhere on the board
RECOVERY1: J1.22; also elsewhere on the board
RECOVERY2: J1.21; also elsewhere on the board
RECOVERY3: J1.20; also elsewhere on the board
RECOVERY4: J1.19; also elsewhere on the board
RECOVERY_HIGH: J1.16, R14.1
UART4_RX: J1.39, J2.39, R52.1, TP1.1
UART4_TX: J1.40, J2.40, R51.1, TP2.1
UART8_RX_GPS: J1.4, J2.4
UART8_TX_GPS: J1.5, J2.5
bus_main: D3.2 (A), F1.1, R2.1, R9.1
charging_voltage: D12.2 (A), J3.5, J4.5, R3.1
main: C3.2, C4.2, C5.2, R1.2, U4.4 (-); also elsewhere on the board
recovery: C19.2, C20.2, C21.2, C22.2, C23.2, D2.2 (A), J5.7, J5.8, Q1.1 (S), Q1.2 (S), Q1.3 (S), R4.1, R10.1, R12.1
vdd_ethernet: C16.2, C45.1, FB1.1, R25.2, R26.2, R27.2, R28.2, R29.2, TP4.1, U6.2 (VO), U14.9 (VDDIO)
vdd_lora1: C10.2, C43.2, C44.2, TP6.1, U3.2 (VO), U11.3 (VDD)
vdd_lora2: C18.2, C48.2, C49.2, TP5.1, U7.2 (VO), U13.3 (VDD)

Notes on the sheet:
Mounting Holes
Here, we measure the current and the voltage of the main voltage and voltage of the high_current power source. The current is measured with the current-sense amplifier The voltage is measured with a voltage divider. For this, the following formula applies: measuring_voltage = (R2) / (R1 + R2) * inp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
diff pair 100ohm
Recovery Outputs
Ethernet PHY
LoRa Modules
5V Regulators
CAN Transceivers
Vehicle Bus & Power Input
3.3V Regulators
Core & GPS Board Connector
D12 allows powering the FC via the charging voltage. This can be useful in situations where we like to power the rocket does not use batteries.
flyback?
The vehicle bus connects the FC to the rest of the rocket. This is the main communication and power connection. It features: - charging/supply voltage: not used on the FC but to charge other boards in the rocket - main bus voltage: up to 12.6V from the main battery supply - CAN1 and CAN2 are the CA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
changed to A2 -> higher gain
Buzzer & Misc. IO
changed to A3 -> higher gain
With internal 1.2V regulator
